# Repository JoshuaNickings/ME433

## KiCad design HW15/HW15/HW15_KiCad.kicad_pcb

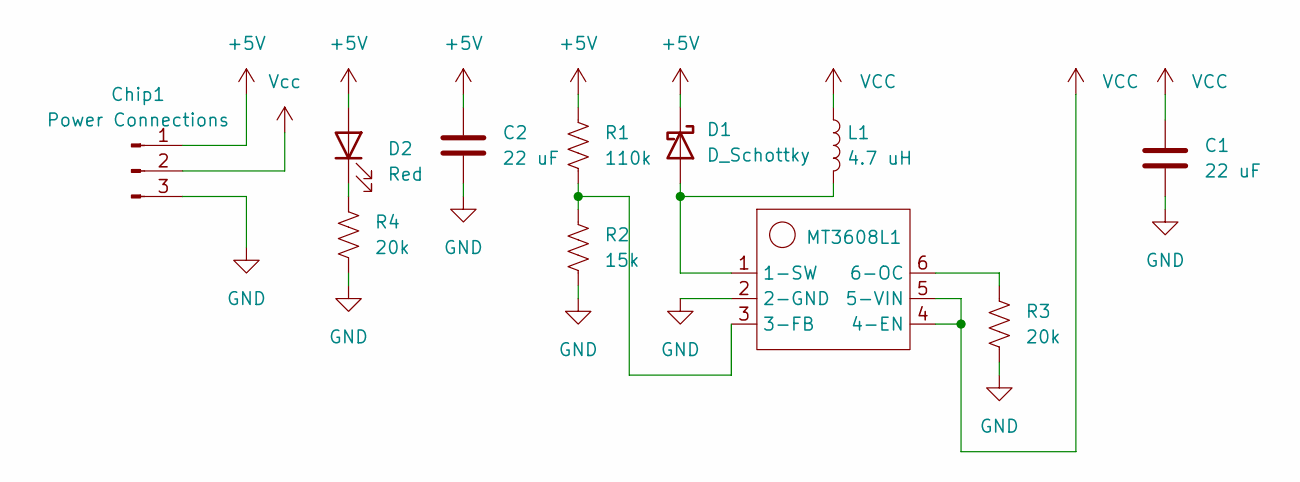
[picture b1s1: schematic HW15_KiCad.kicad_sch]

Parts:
C1, C2: 22 uF; CP_Axial_L11.0mm_D5.0mm_P18.00mm_Horizontal
Chip1: Power Connections; PinSocket_1x03_P2.54mm_Horizontal
D1: D_Schottky; D_0201_0603Metric
D2: Red; LED_D3.0mm
L1: 4.7 uH; LED_D3.0mm
MT3608L1: TSOT-23-6
R1: 110k; R_0805_2012Metric
R2: 15k; R_0805_2012Metric
R3, R4: 20k; R_0805_2012Metric

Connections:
+5V: C2.1, Chip1.1, D1.1 (K), D2.2 (A), R1.1
GND: C1.2, C2.2, Chip1.3, MT3608L1.2 (2-GND), R2.2, R3.2, R4.2
unnamed: D1.2 (A), L1.2, MT3608L1.1 (1-SW)
unnamed: D2.1 (K), R4.1
unnamed: MT3608L1.3 (3-FB), R1.2, R2.1
unnamed: MT3608L1.6 (6-OC), R3.1
Vcc: C1.1, Chip1.2, L1.1, MT3608L1.4 (4-EN), MT3608L1.5 (5-VIN)

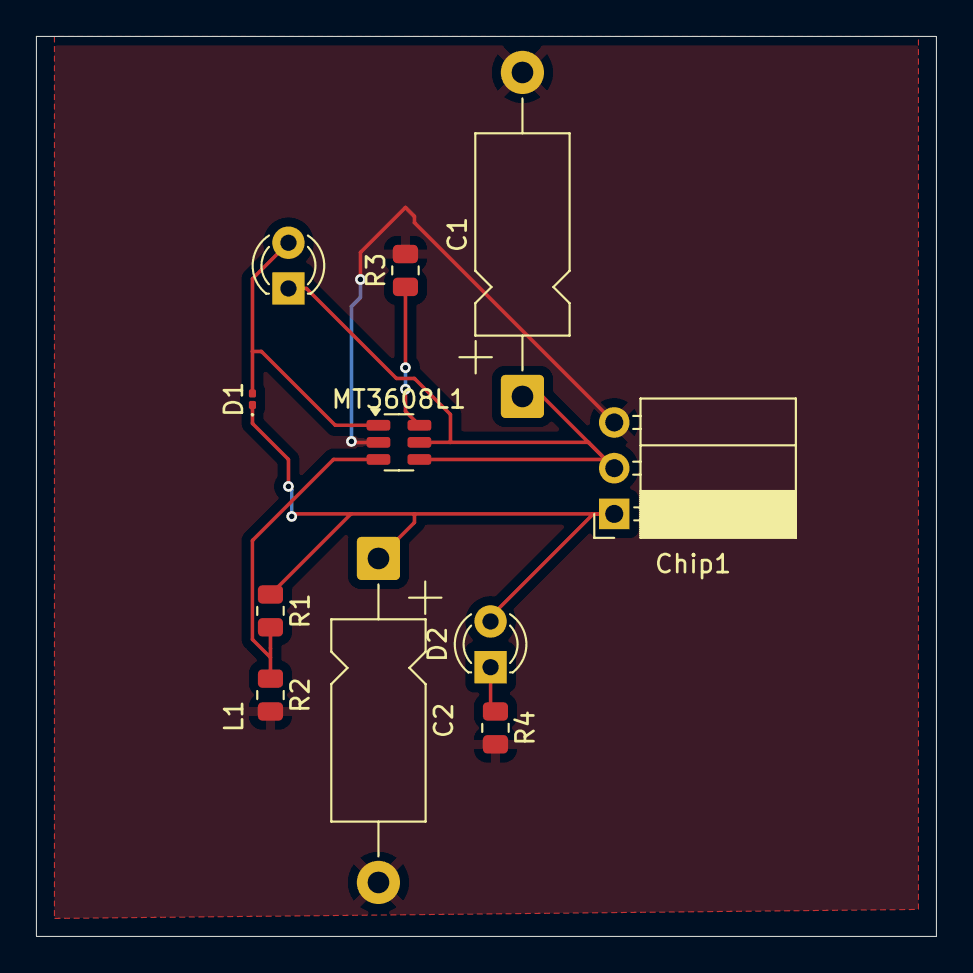
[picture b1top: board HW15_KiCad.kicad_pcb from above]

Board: 2 copper layers, 50.0 x 50.0 mm, 11 parts (0 on the bottom side), 7 nets.

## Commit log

2025-06-01 Establishing Blink + Changing Flash to 1s
2025-06-01 HW2: Corrected Test of Each Example Code
    Hello_GPIO_IRQ has the appropriate edits to allow printf work in screen
    All tests worked! Moving to editing Hello_GPIO_IRQ for the submission of the assignment
2025-06-01 Making Progress on Submission
    Compiles correctly, getting close, but need to remove example code frame and have the count increment upon button press.
2025-06-01 Button Counts on Event Trigger, Need to Edit Event Trigger
    Event triggers on both rising and falling edge, will change so it only counts on rising edge to prevent double counting of button press.
2025-06-01 Completed Assignment
2025-06-01 Parts 1, 2, & 3 of HW3 Done
2025-06-01 Everything Completed
2025-06-01 HW4 First Check
    Working up to the first checkpoint as described in the HW4 assignment declaration and as demonstrated in class.
2025-06-02 Completed HW 4
2025-06-02 Photos of Voltmeter Results
    One image has each horizontal increment as 1 second, the other has it as 400 milliseconds.
2025-06-02 Math and Timing Section Completed
2025-06-02 Created RAM File for Second Part of Assignment
2025-06-02 Limited Success with End of HW5
    Everything works for the most part, but the final sine wave is irregularly blocky. I don't know what to do. The functions write to the RAM properly but I'm not sure where I go wrong when I make the n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
2025-06-03 HW6 Part 1 (Not Complete, But Making Progress!)
2025-06-03 Got GP7 LED to Blink (Has Debug Print Statements)
2025-06-03 Updated Code, Very Close to finishing part 2
    Just need to invert the button output since I wired it incorrectly, otherwise the good works. Will remove debug and heartbeat code for final submission
2025-06-03 Final Code Finished!
2025-06-03 Caught Up Relative to Class
    Code is at the point where the class ended off
2025-06-03 Code seems to be ready; not debugged; I do not have the SSD1306
    Code is ready to test all four milestones of HW 7. However, I did not pick up the chip because I was not in class at the time, so I cannot test the code until i pick it up from Prof. Marchuk (spares 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
2025-06-03 LEDs Working!
    The LED code is working! Just need to figure out how to get the motor working with it!
2025-06-03 Code Prepared, LEDs Work, No RCServo Yet
    Everything for the LED works. The RCServo code works *in theory,* but has yet to be tested. I did not attend class to pick up the RCServo that day, and thus cannot the code until i get the component.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
2025-06-03 HW7 Completed!
    Got the display and was able to verify all the code!
2025-06-04 Code debugged, wiring finished, all works, HW8 Completed!
2025-06-04 HW8 Completed! (Code, Recompild to ensure latest version is pushed)
2025-06-04 HW 9 Tested and Completed!
2025-06-04 Sample Code Understood, Simple Functions Made
2025-06-04 MAF Function Conceptualized
    Testing and debugging has yet to occur
2025-06-04 FFT func & MAF tested, successful
2025-06-04 Filter MAF Completed with Figures Included
2025-06-04 IIR Filter code completed, tested, successful
2025-06-04 FIR Filter completed to the best of my ability
2025-06-04 HW 10 Completed!
    All figure photos uploaded, all code works, everything is ready for submission!
2025-06-05 D-Pad Cursor Control Works! Acceleration Too!
2025-06-05 Got Circle Path to Work! Finished HW 11!
2025-06-06 Uploaded HW12 Assignment Files
    I do not have the physical camera component for wiring yet; all cameras are in use, and extras are unavailable.
    Additionally, I could not find an example Makefile to include with the code, so I am unsure of how to proceed until I find both a camera to wire into my board and a Makefile to compile the C code pro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
2025-06-06 Made Makefile, Compiled Code, Still Bugs
    I was able to create a new C code project on Visual Studio Code and generate the necessary Makefile. Success!
    After editing the Makefile to include all necessary libraries, I compiled the code. Mostly a success!
    There is still a bug; GPIO_IRQ_EDGE_FALL and GPIO_IRQ_EDGE_RISE are undefined despite the appropriate libraries being uploaded.
2025-06-06 Troubleshot Code, HW12 Compiles Correctly
    Code compiled correctly, now I just need the camera then I can proceed with HW 12. Will be scouting for cameras on Friday June 6, 2025 in the lab. Here's hoping!
2025-06-07 Created C Code & Included #Defs
2025-06-07 Input debugging code, testing chip address
2025-06-07 Initialization Function Code Finished
2025-06-07 Data Read Function Made, Untested
2025-06-07 Output Reviewed in Terminal, Accepted (?)
    Accelerations, X, Y, and Z, look appropriate. Note: The values listed as X and Z, according to the chip and its registers, were swapped by me in the output. I did this because the chip is oriented ve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
    Gyroscope values all look off. They all read ~500 when no rotational movement occurs. When rotational movement occurs, the corresponding values approach 0. Unsure of where the error is; I didn't set 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
2025-06-07 Number errors fixed!
    I stored the values in unsigned integers, instead of signed integers. The code has been properly edited and the errors resolved. Great!
2025-06-07 Imported display code, created drawLine() func
    Using the necessary files and code from HW 7, all code needed to use the OLED display *should* be imported and ready for use. Everything compiled correctly, so ideally the code will work too (yet to 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
    Additionally, I wrote up the drawLine() function to be able to create lines with a starting point, length (in pixels), and angle (in degrees).
2025-06-07 DrawLine() Test and Debugged
    Inverted the Y values to match the inverted Y of the display.
2025-06-07 HW 13 Completed!
    Removed inverted y axis in draw line function because it resulted in incorrect pointing for the final code (maybe values are double inverted, so they cancel out)
    Otherwise, everything works as intended!
2025-06-08 HW 14 Files&Prep Finished! Awaiting Prints
    Once the parts are printed and assembled, I will take more pictures of the final robot! Exciting! The CAD took over 12 hours to complete.
2025-06-08 Prints Printed, Assembly Assembled, HW 15 Done!
    The intended interference fits did not hold the part together, but hot glue created the desired attachment. Looks great!
2025-06-08 Schamtic Finished, Working On CB
2025-06-08 HW 15 FInished! (Roughly)
    The PCB wiring is rough and could be made more efficient, however, I need to prioritize other tasks. As of now, what is submitted meets the assignment criteria, so I will move on!
2025-06-08 Latest Version of Completed Schematics
2025-06-08 Latest Version of Completed Schematics 2
2025-06-09 HW 16 Done! Testing Ver Uploading
    I do not have a motor, so i could not estimate at what duty cycle it begins to turn, but otherwise my H-Bridge control works! Im uploading the version that makes the testing obvious, will uplaod the 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
2025-06-09 Proper Finished Code Uploaded; HW 16 Done!
2025-06-09 Best Attempt at Wrapping Up
    Everything should be submitted. I may be getting the jumper cables I purchased for HW 12 (which will allow me to do HW 17 as well) tomorrow, but it is unlikely I will have enough time to complete bot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
